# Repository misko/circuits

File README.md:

# prompt2device

**Prompt to device:** give an agent a plain-language hardware brief, work
through explicit design, review, and physical-test cycles, and finish with the
artifacts needed to manufacture the device—not merely a plausible CAD image.

## Quick start

### 1. Give the PCB skill a brief

```text
/pcb-design 3S LiPo input → 4× USB-A outputs at 5 V / 1.5 A each + 1× USB-C output at 5 V / 5 A.
```

### 2. See fabricated examples

These two projects show the path from a plain-English request to electrical
CAD, mechanical CAD, and fabricated hardware. The prompt cells preserve the
compact original wording; the links retain the corresponding design-lineage
records. Photographs are bench evidence, not production-qualification claims.
Exact provenance and claim limits are in
[`fabricated-examples.md`](docs/fabricated-examples.md).

|  | **Pluto eight-way fast switch** | **3S LiPo USB power board** |
|---|---|---|
| **Prompt** | [“we want a high speed 8 antenna switching board that can be programmed by the rpi4 and run with a pluto+”](archived_projects/pluto-rx2-8way/01_docs/BRIEF.md#original-prompt) | [“Please from scratch start a new project, and lets design a board that takes 3S lipo XT60 power as input , and outputs 3 x USB A ports (2.5A max) and 1 x USB C port (6A max).”](archived_projects/usb-power-3s/01_docs/BRIEF.md#original-prompt) |
| **PCB rendering** |  |  |
| **Enclosure rendering** |  |  |
| **Fabricated board** |  |  |
| **Board in enclosure** |  |  |
| **Bench setup** |  |  |

[`pluto-rx2-8way-v5`](projects/pluto-rx2-8way-v5/) is the fabricated
eight-way RF switch board. Its immutable PCB design archive is
[`v0.2.1-2026-08-14`](projects/pluto-rx2-8way-v5/07_releases/v0.2.1-2026-08-14/),
with a sealed
[3D PCB render](projects/pluto-rx2-8way-v5/07_releases/v0.2.1-2026-08-14/verification/final_iso_3200.png),
and its independently versioned
[`v0.8.0-2026-08-28` enclosure](projects/pluto-rx2-8way-v5/07_enclosure_releases/v0.8.0-2026-08-28/)
has a corresponding
[installed-assembly render](projects/pluto-rx2-8way-v5/07_enclosure_releases/v0.8.0-2026-08-28/renders/installed-assembly.png).
That enclosure remains an honest `INCOMPLETE` candidate pending sliced and
printed fit, retention, connector-service, and thermal tests.
The PCB archive itself predates fabrication and still records
`DO-NOT-ORDER`; RF first-article measurements remain open.
The current human-readable engineering study is
[RF isolation, leakage paths, and a v6 mitigation strategy](projects/pluto-rx2-8way-v5/01_docs/reports/2026-08-27-rf-isolation-and-v6-mitigation.md).

[`usb-hub-3s-v3`](projects/usb-hub-3s-v3/) is the closest existing hardware
to the quick-start brief: three USB-A outputs and one USB-C output rather than
four USB-A outputs. Its latest sealed and fabricated archive is
[`v1.12-2026-07-28`](projects/usb-hub-3s-v3/07_releases/v1.12-2026-07-28/).
The [bring-up journal](projects/usb-hub-3s-v3/01_docs/journal/bringup.md)
records physical v1.12 boards and the replacement assembly's successful
no-load regulation checks; full load, transient, and thermal qualification is
still open.

The exact v1.12 board also has an independently versioned
[`v0.4.0-2026-08-28` enclosure](projects/usb-hub-3s-v3/07_enclosure_releases/v0.4.0-2026-08-28/)
with a corresponding
[installed-assembly render](projects/usb-hub-3s-v3/07_enclosure_releases/v0.4.0-2026-08-28/renders/installed-assembly.png).
Its [authored source and replay instructions](projects/usb-hub-3s-v3/03_src/mechanical/README.md)
remain mutable, while the release is an immutable `INCOMPLETE` candidate:
structural and collision screens pass, but printed fit, connector service,
retention, and thermal evidence remain open.

### 3. Follow the prompt-to-device loop

```text
plain-language brief
  → fact locks and architecture
  → schematic, placement, routing, and enclosure development
  ↺ independent review, correction, regeneration, and measurement
  → sealed fabrication and mechanical artifacts
  → first article, physical findings, and the next development cycle
```

Today the governed output can include:

- native KiCad schematics and a rendered schematic PDF;
- the routed KiCad PCB plus Gerbers, drill files, BOM, and CPL for fabrication;
- top, bottom, and 3D PCB renders plus a STEP assembly;
- when mechanical work is selected, enclosure source, printable STLs, assembly
  renders, and clearance evidence; and
- governed Markdown investigations under each project's `01_docs/reports/`.

The pipeline already uses board-level CAD/assembly twins as verification
instruments. Governed firmware releases and an integrated product-level digital
twin are forward work, tracked by
[IMP-234](improvements.md#imp-234--firmware-release-stream) and
[IMP-236](improvements.md#imp-236--prompt-to-device-product-composition-and-digital-twin).

## What this repository is

`prompt2device` is a code-first prompt-to-device engineering system. It turns a
user brief into generated KiCad source, bounded routing candidates,
independently graded fabrication evidence, immutable releases, printable
enclosures, and measured first-article records.

The product is the workflow under [`skills/`](skills/). Boards under
[`projects/`](projects/) are its active applications; sealed release folders
are immutable evidence, not templates to copy.

## Manual commissioning

Clone the repository, create a branch, and save the user's original request as
a UTF-8 text file:

```bash
git clone https://github.com/misko/prompt2device.git
cd prompt2device
git switch -c codex/my-board
```

Create the governed project scaffold and choose its capability profile:

```bash
python3 skills/pcb-design/scripts/commission_project.py my-board \
  --brief-file /path/to/original-brief.txt \
  --signal-integrity ordinary \
  --assembly jlcpcb \
  --firmware forbidden \
  --target design
```

Use `high_speed_digital` for USB and similar controlled digital links. Use
`rf` only when the board intentionally carries RF/microwave signals. Add
`--foreign-mating` when the floorplan consumes geometry from third-party
hardware. Run the command with `--help` for enclosure and target options.
Here `--assembly jlcpcb` selects the populated JLCPCB PCBA evidence path, not
merely bare-board fabrication.

The command reports `PCB-SCAFFOLD OK` and leaves `PCB-COMMISSION` explicitly
`INCOMPLETE`. It preserves the prompt and creates an executable commission
hold; it does not accept requirements, adopt the seeded schema examples, or
run a board producer.

Inspect the selected lifecycle before spending engineering time:

```bash
python3 skills/pcb-design/scripts/skill_reference_router.py \
  --profile projects/my-board/01_docs/capability-profile.json \
  --at-stage PCB-COMMISSION \
  --json
```

Then give Codex this instruction:

```text
Read and follow skills/pcb-design/SKILL.md for projects/my-board. Preserve the
original brief, close the commission fact locks, and stop at the first evidence
or operator checkpoint. Do not create firmware unless the brief explicitly
asks.
```

Do not run `rebuild_all.sh` yet. The scaffold contains visible schema examples
and `01_docs/COMMISSIONING-HOLD.md`; both rebuild conductors refuse to run until
the commission boundary is reviewed and that marker is deliberately removed.

Start with [`skills/pcb-design/SKILL.md`](skills/pcb-design/SKILL.md). Its
canonical lifecycle and runnable command map is
[`execution-graph.md`](skills/pcb-design/references/execution-graph.md).

## How execution is structured

The repository deliberately separates three layers:

```text
capability profile
  -> disclosure graph (what stages/references are selected)
  -> project conductor (what bounded commands actually run)
  -> owning gates (what exact subjects passed)
  -> review/seal/publication/physical claims
```

- The router is planning only. Its output is never execution evidence.
- `projects/<name>/03_src/rebuild_all.sh` is the full source/schematic
  conductor. It intentionally pauses at review and operator checkpoints.
- `rebuild_reuse.sh` is the deterministic route-authority replay when the
  schematic is unchanged; `route.yaml` selects the authenticated source.
- Fresh route exploration is a separate candidate workflow; canonical rebuild
  replays the authenticated route source selected by `route.yaml`.
- Layout seal, PCB release seal, publication, ordering, and first article are
  different claims with different owners.

The declarative lifecycle is:

```text
commission -> architecture -> sourcing
  -> schematic -> placement -> routing -> layout seal
  -> fabrication -> assembly verification
  -> release review -> release seal
  -> publication | first article -> production
```

RF context/source/realized/fabrication stages and foreign-mating import are
conditional branches. High-speed digital composes inside the ordinary stages.
Enclosures have an implemented parallel **INCOMPLETE-candidate** release stream
and may bind an unchanged PCB release without resealing it. Higher readiness
still requires the enclosure skill's recomputable CAD and physical evidence.
Firmware is currently an explicit handoff,
not a governed release stream; [IMP-234](improvements.md#imp-234--firmware-release-stream)
tracks that missing boundary.

## Skills and authority

| Skill | Owns |
|---|---|
| [`pcb-design`](skills/pcb-design/SKILL.md) | Commission, lifecycle composition, backtracking, reviews, release seal, publication, first article. |
| [`kicad-pcb`](skills/kicad-pcb/SKILL.md) | TSX/KiCad schematic conversion, netlist/parity, placement, geometry, routing, DRC, SI/RF realization. |
| [`jlcpcb-fab`](skills/jlcpcb-fab/SKILL.md) | Gerber/drill/BOM/CPL, stock/population/rotation, JLC CAD twin, manufacturer staging, bring-up cards. |
| [`pcb-enclosure`](skills/pcb-enclosure/SKILL.md) | Mechanical commission, PCB interface binding, independent fasteners, motion/clearance, mesh/physical evidence, enclosure releases. |
| [`shopping-list`](skills/shopping-list/SKILL.md) | Provenance-bound purchase lists for self-supplied parts. |

Authority is singular. A skill links to another owner's procedure rather than
copying it. Project `contracts.md` files own exact artifact membership. Script
`--help` text owns exact flags. [`improvements.md`](improvements.md) tracks
work and rationale but never overrides an executable gate or accepted ADR.

## Repository map

| Path | Purpose |
|---|---|
| [`skills/`](skills/) | Reusable workflow, references, tools, and project templates. |
| [`projects/`](projects/) | Active boards, including manufactured and still-evolving designs. |
| [`archived_projects/`](archived_projects/) | Retired scaffolds and frozen regression/history units. |
| [`docs/`](docs/) | Documentation index, accepted ADRs, measured proof, and historical context. |
| [`tests/`](tests/) | Clean and known-bad fixtures proving gates can both pass and fail. |
| [`external_hardware/`](external_hardware/) | Measured/cited facts about foreign devices this repo must mate with. |
| [`improvements.md`](improvements.md) | Forward work registry and retained improvement history. |

See [`docs/README.md`](docs/README.md) for the documentation authority map.

## Design model

The board is generated from committed human-owned source:

- TSX/tscircuit is the standard schematic authoring front end.
- Shared scripts convert the circuit, generate KiCad geometry/rules, and grade
  exact identities. Per-board source is configuration, not a copied backend.
- KiCad's Python API owns geometry and saves; `kicad-cli` owns headless
  ERC/DRC/netlist/export checks.
- Routing operates on immutable candidates. Only a clean, independently graded
  candidate can become the promoted route chain.
- Generated `04_kicad/` is a mutable current snapshot and is never hand-source
  authority. Immutable history lives under release streams.

This makes design changes diffable and rebuildable. It also means a generator
defect can become a physical defect, so freshness, parity, nonzero coverage,
registered models, and independent review are first-class gates.

## Claims and releases

A release is an immutable reviewed candidate archive. It is not automatically
an order event. A design can be electrically sound and sealed while remaining
`DO-NOT-ORDER` because stock, uploader selections, physical fit, or first-
article evidence is owed.

PCB and enclosure versions are independent streams. Current enclosure release
tooling publishes immutable `INCOMPLETE` candidates bound to one exact PCB
release without forcing that PCB to be resealed; it does not yet publish a
higher readiness claim from caller-supplied scope status.
A future firmware stream, exact product lock, and integrated product-level
digital twin remain tracked work, not current release authority.

## Toolchain

Core documentation and planning use normal Python 3. KiCad operations require
the KiCad-bundled Python where `import pcbnew` succeeds plus `kicad-cli`.
TSX generation requires the pinned tscircuit/Bun environment. Fresh routing
requires the configured KiCadRoutingTools installation; replaying a selected
authenticated route authority does not.

Python entry points expose `--help`; shell-conductor forms are documented in
the execution graph. Use the owning current command rather than copying an old
invocation from a project journal.

## Validate a workflow change

At minimum:

```bash
python3 skills/pcb-design/scripts/skill_authority_check.py
python3 tests/t1_skill_progressive_disclosure.py
python3 tests/t1_pcb_documentation.py
python3 scripts/contracts_audit.py --walk --root skills/pcb-design
```

Run the domain suites affected by the change, then commit at a green boundary.

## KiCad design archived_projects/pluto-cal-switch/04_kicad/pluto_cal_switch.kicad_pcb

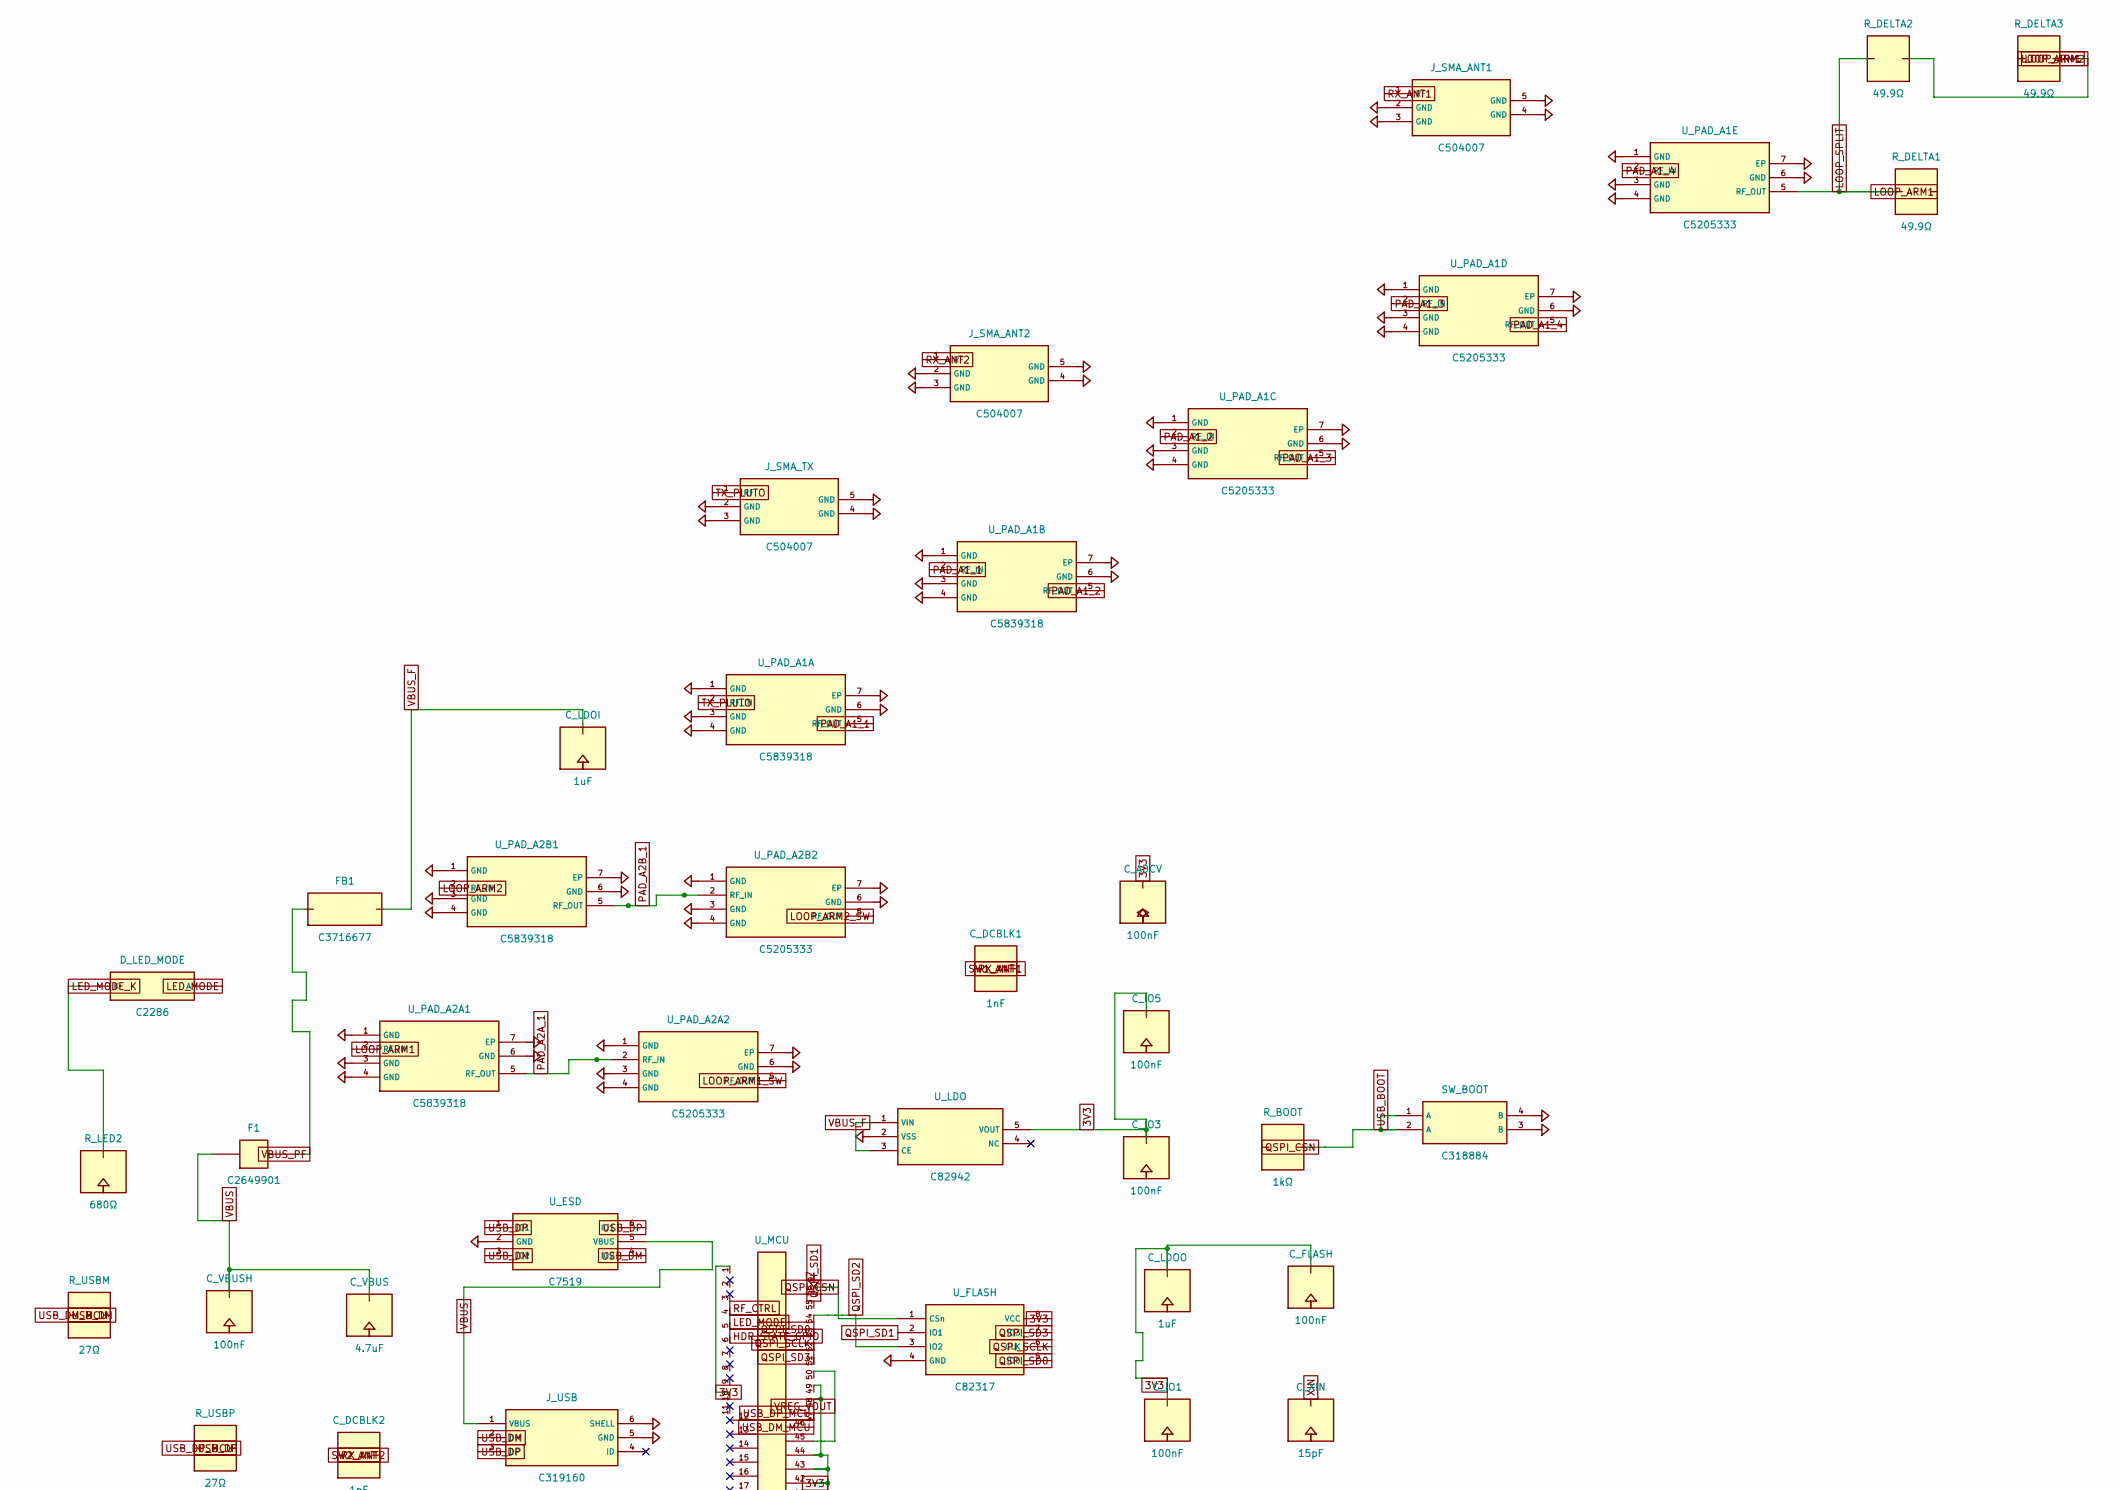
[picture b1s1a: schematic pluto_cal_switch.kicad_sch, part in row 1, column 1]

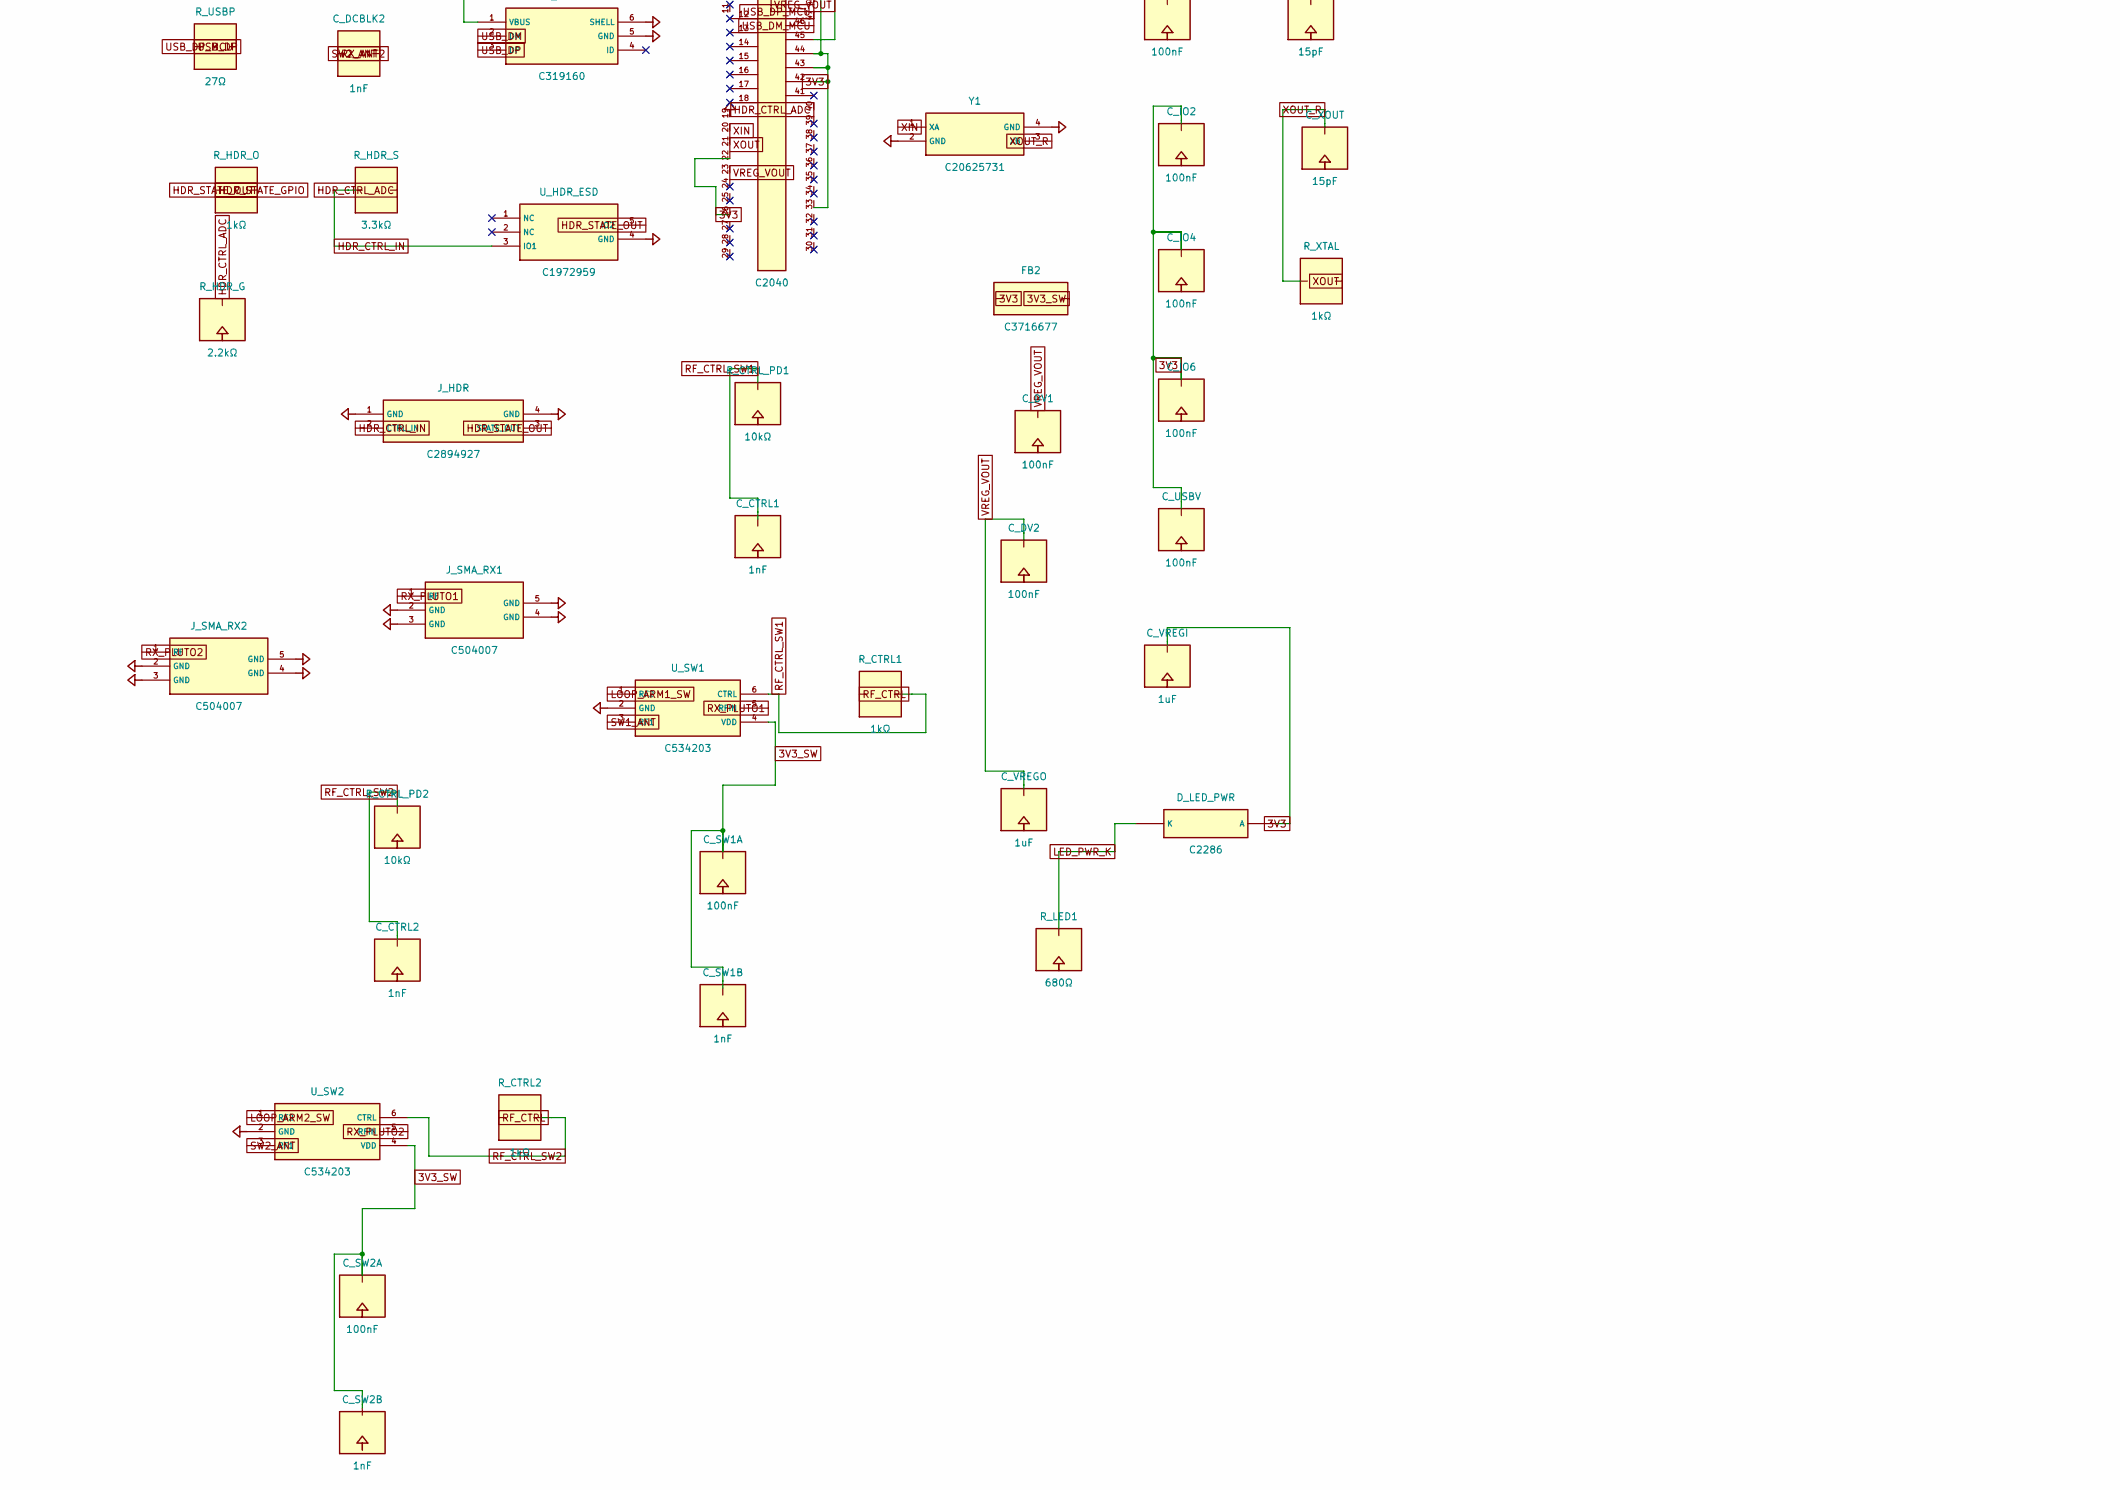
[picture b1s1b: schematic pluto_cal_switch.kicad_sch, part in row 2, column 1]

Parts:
C_ADCV: 100nF; C_0402_1005Metric
C_CTRL1, C_CTRL2: 1nF; C_0402_1005Metric
C_DCBLK1, C_DCBLK2: 1nF; C_0402_1005Metric_RF
C_DV1, C_DV2: 100nF; C_0402_1005Metric
C_FLASH: 100nF; C_0402_1005Metric
C_IO1, C_IO2, C_IO3, C_IO4, C_IO5, C_IO6: 100nF; C_0402_1005Metric
C_LDOI: 1uF; C_0402_1005Metric
C_LDOO: 1uF; C_0402_1005Metric
C_SW1A, C_SW2A: 100nF; C_0402_1005Metric
C_SW1B, C_SW2B: 1nF; C_0402_1005Metric
C_USBV: 100nF; C_0402_1005Metric
C_VBUS: 4.7uF; C_0805_2012Metric
C_VBUSH: 100nF; C_0402_1005Metric
C_VREGI: 1uF; C_0402_1005Metric
C_VREGO: 1uF; C_0402_1005Metric
C_XIN: 15pF; C_0402_1005Metric
C_XOUT: 15pF; C_0402_1005Metric
D_LED_MODE: C2286; LED_0603_1608Metric
D_LED_PWR: C2286; LED_0603_1608Metric
F1: C2649901; Fuse_1812_4532Metric
FB1, FB2: C3716677; C_0805_2012Metric
J_HDR: C2894927; PinHeader_1x04_P2.54mm_Vertical
J_SMA_ANT1, J_SMA_ANT2: C504007; SMA_Vertical_5.08sq_D1.4
J_SMA_RX1, J_SMA_RX2: C504007; SMA_Vertical_5.08sq_D1.4
J_SMA_TX: C504007; SMA_Vertical_5.08sq_D1.4
J_USB: C319160; USB_Micro-B_XKB_U254-051T
R_BOOT: 1kΩ; R_0402_1005Metric
R_CTRL1, R_CTRL2: 1kΩ; R_0402_1005Metric
R_CTRL_PD1, R_CTRL_PD2: 10kΩ; R_0402_1005Metric
R_DELTA1, R_DELTA2, R_DELTA3: 49.9Ω; R_0402_1005Metric_RF
R_HDR_G: 2.2kΩ; R_0402_1005Metric
R_HDR_O: 1kΩ; R_0402_1005Metric
R_HDR_S: 3.3kΩ; R_0402_1005Metric
R_LED1, R_LED2: 680Ω; R_0402_1005Metric
R_USBM: 27Ω; R_0402_1005Metric
R_USBP: 27Ω; R_0402_1005Metric
R_XTAL: 1kΩ; R_0402_1005Metric
SW_BOOT: C318884; SW_Push_1P1T_XKB_TS-1187A
U_ESD: C7519; SOT-23-6
U_FLASH: C82317; SOIC-8_5.3x5.3mm_P1.27mm
U_HDR_ESD: C1972959; SOT-553
U_LDO: C82942; SOT-23-5
U_MCU: C2040; QFN-56-1EP_7x7mm_P0.4mm_EP3.2x3.2mm
U_PAD_A1A, U_PAD_A1B, U_PAD_A2A1, U_PAD_A2B1: C5839318; MCLP-6-EP_2x2_P0.65_MC1630
U_PAD_A1C, U_PAD_A1D, U_PAD_A1E, U_PAD_A2A2, U_PAD_A2B2: C5205333; MCLP-6-EP_2x2_P0.65_MC1630
U_SW1, U_SW2: C534203; TSNP-6_0.7x1.1_P0.4_NSMD
Y1: C20625731; Crystal_SMD_3225-4Pin_3.2x2.5mm

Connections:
3V3: C_ADCV.1, C_FLASH.1, C_IO1.1, C_IO2.1, C_IO3.1, C_IO4.1, C_IO5.1, C_IO6.1, C_LDOO.1, C_USBV.1, C_VREGI.1, D_LED_PWR.2 (A), FB2.1, U_FLASH.8 (VCC), U_LDO.5 (VOUT), U_MCU.1, U_MCU.10, U_MCU.22, U_MCU.26, U_MCU.33, U_MCU.42, U_MCU.43, U_MCU.44, U_MCU.48, U_MCU.49
3V3_SW: C_SW1A.1, C_SW1B.1, C_SW2A.1, C_SW2B.1, FB2.2, U_SW1.4 (VDD), U_SW2.4 (VDD)
GND: C_ADCV.2, C_CTRL1.2, C_CTRL2.2, C_DV1.2, C_DV2.2, C_FLASH.2, C_IO1.2, C_IO2.2, C_IO3.2, C_IO4.2, C_IO5.2, C_IO6.2, C_LDOI.2, C_LDOO.2, C_SW1A.2, C_SW1B.2, C_SW2A.2, C_SW2B.2, C_USBV.2, C_VBUS.2, C_VBUSH.2, C_VREGI.2, C_VREGO.2, C_XIN.2, C_XOUT.2, J_HDR.1 (GND), J_HDR.4 (GND), J_SMA_ANT1.2 (GND), J_SMA_ANT1.3 (GND), J_SMA_ANT1.4 (GND), J_SMA_ANT1.5 (GND), J_SMA_ANT2.2 (GND), J_SMA_ANT2.3 (GND), J_SMA_ANT2.4 (GND), J_SMA_ANT2.5 (GND), J_SMA_RX1.2 (GND), J_SMA_RX1.3 (GND), J_SMA_RX1.4 (GND), J_SMA_RX1.5 (GND), J_SMA_RX2.2 (GND), J_SMA_RX2.3 (GND), J_SMA_RX2.4 (GND), J_SMA_RX2.5 (GND), J_SMA_TX.2 (GND), J_SMA_TX.3 (GND), J_SMA_TX.4 (GND), J_SMA_TX.5 (GND), J_USB.5 (GND), J_USB.6 (SHELL), R_CTRL_PD1.2, R_CTRL_PD2.2, R_HDR_G.2, R_LED1.2, R_LED2.2, SW_BOOT.3 (B), SW_BOOT.4 (B), U_ESD.2 (GND), U_FLASH.4 (GND), U_HDR_ESD.4 (GND), U_LDO.2 (VSS), U_MCU.19, U_MCU.57, U_PAD_A1A.1 (GND), U_PAD_A1A.3 (GND), U_PAD_A1A.4 (GND), U_PAD_A1A.6 (GND), U_PAD_A1A.7 (EP), U_PAD_A1B.1 (GND), U_PAD_A1B.3 (GND), U_PAD_A1B.4 (GND), U_PAD_A1B.6 (GND), U_PAD_A1B.7 (EP), U_PAD_A1C.1 (GND), U_PAD_A1C.3 (GND), U_PAD_A1C.4 (GND), U_PAD_A1C.6 (GND), U_PAD_A1C.7 (EP), U_PAD_A1D.1 (GND), U_PAD_A1D.3 (GND), U_PAD_A1D.4 (GND), U_PAD_A1D.6 (GND), U_PAD_A1D.7 (EP), U_PAD_A1E.1 (GND), U_PAD_A1E.3 (GND), U_PAD_A1E.4 (GND), U_PAD_A1E.6 (GND), U_PAD_A1E.7 (EP), U_PAD_A2A1.1 (GND), U_PAD_A2A1.3 (GND), U_PAD_A2A1.4 (GND), U_PAD_A2A1.6 (GND), U_PAD_A2A1.7 (EP), U_PAD_A2A2.1 (GND), U_PAD_A2A2.3 (GND), U_PAD_A2A2.4 (GND), U_PAD_A2A2.6 (GND), U_PAD_A2A2.7 (EP), U_PAD_A2B1.1 (GND), U_PAD_A2B1.3 (GND), U_PAD_A2B1.4 (GND), U_PAD_A2B1.6 (GND), U_PAD_A2B1.7 (EP), U_PAD_A2B2.1 (GND), U_PAD_A2B2.3 (GND), U_PAD_A2B2.4 (GND), U_PAD_A2B2.6 (GND), U_PAD_A2B2.7 (EP), U_SW1.2 (GND), U_SW2.2 (GND), Y1.2 (GND), Y1.4 (GND)
HDR_CTRL_ADC: R_HDR_G.1, R_HDR_S.2, U_MCU.40
HDR_CTRL_IN: J_HDR.2 (CTRL_IN), R_HDR_S.1, U_HDR_ESD.3 (IO1)
HDR_STATE_GPIO: R_HDR_O.1, U_MCU.6
HDR_STATE_OUT: J_HDR.3 (STATE_OUT), R_HDR_O.2, U_HDR_ESD.5 (IO2)
LED_MODE: D_LED_MODE.2 (A), U_MCU.5
LED_MODE_K: D_LED_MODE.1 (K), R_LED2.1
LED_PWR_K: D_LED_PWR.1 (K), R_LED1.1
LOOP_ARM1: R_DELTA1.2, R_DELTA3.1, U_PAD_A2A1.2 (RF_IN)
LOOP_ARM1_SW: U_PAD_A2A2.5 (RF_OUT), U_SW1.1 (RF2)
LOOP_ARM2: R_DELTA2.2, R_DELTA3.2, U_PAD_A2B1.2 (RF_IN)
LOOP_ARM2_SW: U_PAD_A2B2.5 (RF_OUT), U_SW2.1 (RF2)
LOOP_SPLIT: R_DELTA1.1, R_DELTA2.1, U_PAD_A1E.5 (RF_OUT)
PAD_A1_1: U_PAD_A1A.5 (RF_OUT), U_PAD_A1B.2 (RF_IN)
PAD_A1_2: U_PAD_A1B.5 (RF_OUT), U_PAD_A1C.2 (RF_IN)
PAD_A1_3: U_PAD_A1C.5 (RF_OUT), U_PAD_A1D.2 (RF_IN)
PAD_A1_4: U_PAD_A1D.5 (RF_OUT), U_PAD_A1E.2 (RF_IN)
PAD_A2A_1: U_PAD_A2A1.5 (RF_OUT), U_PAD_A2A2.2 (RF_IN)
PAD_A2B_1: U_PAD_A2B1.5 (RF_OUT), U_PAD_A2B2.2 (RF_IN)
QSPI_CSN: R_BOOT.1, U_FLASH.1 (CSn), U_MCU.56
QSPI_SCLK: U_FLASH.6 (CLK), U_MCU.52
QSPI_SD0: U_FLASH.5 (IO0), U_MCU.53
QSPI_SD1: U_FLASH.2 (IO1), U_MCU.55
QSPI_SD2: U_FLASH.3 (IO2), U_MCU.54
QSPI_SD3: U_FLASH.7 (IO3), U_MCU.51
RF_CTRL: R_CTRL1.1, R_CTRL2.1, U_MCU.4
RF_CTRL_SW1: C_CTRL1.1, R_CTRL1.2, R_CTRL_PD1.1, U_SW1.6 (CTRL)
RF_CTRL_SW2: C_CTRL2.1, R_CTRL2.2, R_CTRL_PD2.1, U_SW2.6 (CTRL)
RX_ANT1: C_DCBLK1.1, J_SMA_ANT1.1 (RF)
RX_ANT2: C_DCBLK2.1, J_SMA_ANT2.1 (RF)
RX_PLUTO1: J_SMA_RX1.1 (RF), U_SW1.5 (RFIN)
RX_PLUTO2: J_SMA_RX2.1 (RF), U_SW2.5 (RFIN)
SW1_ANT: C_DCBLK1.2, U_SW1.3 (RF1)
SW2_ANT: C_DCBLK2.2, U_SW2.3 (RF1)
TX_PLUTO: J_SMA_TX.1 (RF), U_PAD_A1A.2 (RF_IN)
USB_BOOT: R_BOOT.2, SW_BOOT.1 (A), SW_BOOT.2 (A)
USB_DM: J_USB.2 (DM), R_USBM.1, U_ESD.3 (IO2), U_ESD.4 (IO2)
USB_DM_MCU: R_USBM.2, U_MCU.46
USB_DP: J_USB.3 (DP), R_USBP.1, U_ESD.1 (IO1), U_ESD.6 (IO1)
USB_DP_MCU: R_USBP.2, U_MCU.47
VBUS: C_VBUS.1, C_VBUSH.1, F1.1, J_USB.1 (VBUS), U_ESD.5 (VBUS)
VBUS_F: C_LDOI.1, FB1.2, U_LDO.1 (VIN), U_LDO.3 (CE)
VBUS_PF: F1.2, FB1.1
VREG_VOUT: C_DV1.1, C_DV2.1, C_VREGO.1, U_MCU.23, U_MCU.45, U_MCU.50
XIN: C_XIN.1, U_MCU.20, Y1.1 (XA)
XOUT: R_XTAL.2, U_MCU.21
XOUT_R: C_XOUT.1, R_XTAL.1, Y1.3 (XB)

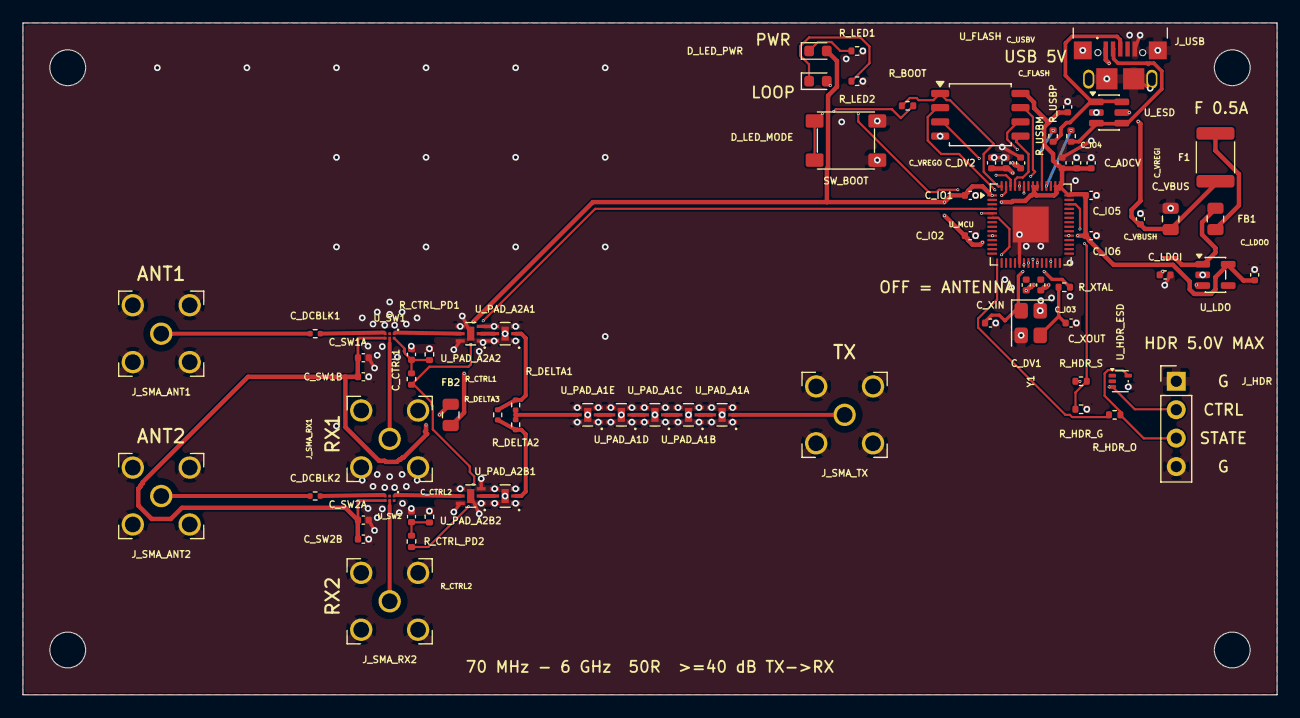
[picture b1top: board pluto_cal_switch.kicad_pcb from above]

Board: 4 copper layers, 112.0 x 60.0 mm, 77 parts (0 on the bottom side), 49 nets.

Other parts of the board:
H1, H2, H3, H4: MountingHole_3.2mm_M3
